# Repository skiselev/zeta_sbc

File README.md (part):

## Introduction

Zeta SBC V2 is a redesigned version of [Zeta SBC](http://www.malinov.com/Home/sergeys-projects/zeta-sbc). Compared to the first version this version features updated MMU with four banks, each one of those banks can be mapped to any 16 KiB page in 1 MiB on-board memory. It adds Z80 CTC which is used for generating periodic interrupts and as a vectored interrupt controller for UART and PPI. The FDC is replaced with 37C65. Compared to FDC9266 used in Zeta SBC it integrates input/output buffers and floppy disk control latch. Additionally 37C65 FDC is easier to obtain than FDC9266. And lastly it is made using CMOS technology and more power efficient than FDC9266

## Pictures

### Complete Board

### Zeta SBC with ParPortProp and a Floppy Drive

(FIXME: Picture shows Zeta SBC V1. Replace with Zeta SBC V2 when available.)

# Specifications

Zeta SBC V2 features following components:

* Z80 CPU
* 16550 UART - for connecting a console
* 8255 PPI - can be used for attaching a ParPortProp board, a hard drive using PPIDE or controlling some external devices
* Z80 CTC - can be used to generate periodic interrupts, and as an interrupt controller for UART and PPI
* Western Digital WD37C65, SMC FDC37C65, or GoldStar GM82C765B floppy disk controller.
* 512 KiB of battery backed SRAM
* 512 KiB of flash memory
* RTC

Zeta SBC V2 is compact and easy to build:

* Footprint of an 3.5" floppy drive (100 mm x 170.18 mm) and PCB can be mounted under a 3.5" drive.
* Uses only through hole components.
* Assumes using commonly available 3.5" floppy drives (not many people have 5.25" drives and even less 8" ones). Although it should work with 5.25" drives too.
* Only 2 configuration jumpers.
* Easy to use flash memory instead of UV EPROM.
* PCB mounted connectors, no need to build cables.
* Uses widely available components
* An easy way to get a "taste" of CP/M era computing.

# Hardware Documentation

File downloads are at the bottom of this page.

## KiCad Design Files

[Zeta SBC V2 - KiCad - 2.0.zip](files/Zeta%20SBC%20V2%20-%20KiCad%20-%202.0.zip)

## Schematic

[Zeta SBC V2 - Schematic - Color - 2.0.pdf](files/Zeta%20SBC%20V2%20-%20Schematic%20-%20Color%20-%202.0.pdf)

### PCB Version 2.0

[Zeta SBC V2 - Board - Color - 2.0.pdf](files/Zeta%20SBC%20V2%20-%20Board%20-%20Color%20-%202.0.pdf)

[Zeta SBC V2 - Gerber - 2.0.zip](files/Zeta%20SBC%20V2%20-%20Gerber%20-%202.0.zip)

## Input/Output Ports

* 20h - 23h (aliases 24h - 27h) - CTC Registers
  - 20h: Channel 0
  - 21h: Channel 1
  - 22h: Channel 2
  - 23h: Channel 3
  - See **Interrupts** section for Zeta SBC V2 specific CTC implementation and programming notes
* 28h (aliases 29h - 2Fh) - FDC CCR Register
  - Write only
  - FIXME: Add detailed description
* 30h (aliases 32h, 34h, 36h) - FDC Main Status Register
* 31h (aliases 33h, 35h, 37h) - FDC Data Register
* 38h (aliases 39h - 3Fh)
  - Write - FDC Diginal Output Register (DOR), also known as latch.
    + FIXME: Add detailed description
  - Read - Pulse FDC's /DACK and TC control lines
    + This port should be read following FDC data transfer command (read, write, format, etc.) to properly terminate data transfer.
* 60h-63h (alias 64h-67h) - PPI Registers
* 68h-6Fh - UART Registers
* 70h (aliases 71h-77h) - RTC Registers
  - Write:
    + Bits 0-3 - unused
    + Bit 4 - RTC Chip Enable
    + Bit 5 - RTC Write Enable
    + Bit 6 - RTC Clock
    + Bit 7 - RTC Input
  - Read:
    + Bit 0 - RTC Output
    + Bits 1-5 - unused
    + Bit 6 - Configuration Jumper (JP1)
    + Bit 7 - Disk Changed (DC) output from floppy drive. This can be used by the OS to detect floppy disk change. In such case CP/M should be warm rebooted.
* 78h-7Bh (alias 7Ch-7Fh) - Memory page select registers.
  - Write only
  - 78h - MPGSEL_0 - Page select register for bank #0 (0000h - 3FFFh)
  - 79h - MPGSEL_1 - Page select register for bank #1 (4000h - 7FFFh)
  - 7Ah - MPGSEL_2 - Page select register for bank #2 (8000h - 0BFFFh)
  - 7Bh - MPGSEL_3 - Page select register for bank #3 (0C000h - 0FFFFh)
  - Note: While these registers implemented as 8-bit registers, only 7 lower bits are decoded on board. 6 of these are actually used by on board memory, which contains of 64 pages, 16 KiB each.
* 7Ch (aliases 7Dh-7Fh) - MPGENA - Enable memory paging
  - Bits 0:
    + 0 = Disable memory paging (default after reset). When memory paging is disabled the memory page 0 (lower 16 KiB of the Flash ROM) is mapped to all banks.
    + 1 = Enable memory paging. Make sure that memory page select registers are configured properly before enabling paging.
  - Bits 1-7 - unused

## Memory

Zeta SBC V2 features a 512 KiB Flash ROM, and 512 KiB SRAM. The Flash ROM is used for the boot loader, monitor, OS (CP/M and ZSDOS at this point), and ROM disk. The SRAM is battery-backed, and is used for applications and for a RAM disk.

### Memory Banks and Paging

The 64 KiB Z80 memory address space is divided into four 16 KiB memory banks:

* Bank #0 (0000h - 3FFFh
* Bank #1 (4000h - 7FFFh)
* Bank #2 (8000h - 0BFFFh)
* Bank #3 (0C000h - 0FFFFh)

The physical memory (512 KiB Flash ROM and 512 KiB SRAM) is divided into 16 KiB pages:

* Pages 0 - 31 are mapped to the Flash ROM: page #0 starts at ROM address 00000h, and page #31 ends at ROM address 7FFFFh.
* Pages 32 - 63 are mapped to the SRAM: page #32 starts at RAM address 00000h, and page #63 ends at RAM address 7FFFFh.

Page select registers are used to map physical memory pages to the banks in Z80 address space:

* MPGSEL_0 (78h) - Page select register for bank #0
* M PGSEL_1 (79h) - Page select register for bank #1
* M PGSEL_2 (7Ah) - Page select register for bank #2
* M PGSEL_3 (7Bh) - Page select register for bank #3

Following a power on or a hard reset the memory paging mechanism is disabled, and memory address lines MA19 - MA14 are pulled down. So that page #0 (ROM addresses 00000h to 03FFF) is mapped to all four banks. That page should contain a boot loader that (among other things) configures and enables memory paging. Once page select registers are configured properly the memory paging can be enabled by setting bit 1 of MPGENA (7Ch) register.

### Programming Notes

1. The content of page select registers is unknown after a power on or a reboot. These registers need to be initialized before enabling memory paging. During the initialization the page select register for bank #0 needs to be set to page #0. So that CPU continues to execute instructions from that page.
2. The page select registers are implemented as 8-bit registers. Only 7 lower bits are decoded by Zeta SBC V2 memory chip select logic, and only 6 lower bits are actually used to address the memory. For future compatibility it is recommended that two higher bits of page select registers will be set to

## Interrupts

Zeta SBC V2 uses CTC as the source of vectored interrupts. For interrupts to function properly Z80 needs to be set to **interrupt mode 2**.

* Channels 0 and 1 are chained together. So that channel 1 can be used to generate low-frequency periodic interrupts:
  - Channel's 0 CLK/TG input is connected to UART_CLK/2 signal (921.6 kHz frequency)
  - Channel's 1 CLK/TG input in connected to c hannel's 0 ZC/TO output
* Channels 2 and 3 are connected to UART and FDC interrupt outputs. They can be used to generate vectored interrupts for these controllers:
  - Channel's 2 CLK/TG input is connected to UART interrupt output
  - Channel's 3 CLK/TG input is connected to 8255 PPI port PC3. This port is used as the interrupt output in PPI modes 1 and 2.

### Programming CTC to Generate Periodic Interrupts

CTC can generate periodic interrupts by dividing CTC clock (921.6 kHz) using channels 0 and 1 configured in counter mode. The CTC clock is connected to the trigger input of channel 0, and the ZC (zero count) output of channel 0 is connected the trigger input of channel 1. So that channel 0 will divide the clock, and the resulting signal will be divided further using channel 1.

In this example channel 0 is programmed with time constant of 256, so it will divide the input clock by 256, resulting in 3.6 kHz pulses. The channel 1 is programmed with down counter of 240, and will divide 3.6 kHz clock by 240, resulting in 15 Hz signal. That channel is also programmed to generate an interrupt every time counter reaches 0.

* Output `01000111 `to the channel 0. Configure the channel in the counter mode.
* Output `00000000&#xA0;`to the channel 0. Set the time constant to 256.
* Output `11000111 `to the channel 1. Configure the channel in the counter mode and enable interrupt when counter reaches 0.
* Output `11110000` to the channel 1. Set the time constant to 240, so that the interrupt will be generated every 1/15 of a second.
* Output `VVVVV000&#xA0;`to the channel 0. Set bits 7-3 of the interrupt vector. Bits 15-8 are set to the value of I register, bits 2 and 1 are set to the CTC channel number that caused the interrupt. Bit 0 is always 0. Note that each interrupt vector takes 2 bytes of memory and it should start on an even address.

### Programming CTC as an Interrupt Controller

CTC can be used as interrupt controller for UART and 8255 PPI using channels 2 and 3 respectively. In this case a CTC channel needs to be programmed for counter mode operation with time constant of 1. So that the first transition on CLK/TG input will result in counter going to 0 and CTC generating an interrupt.

* Output `110L0111` to the selected channel. This configures the channel in the counter mode with interrupts enabled. Bit 4 (L) sets the triggering edge: 0 - falling edge; 1 - rising edge.
* Output `00000001` to the selected channel. This loads value 1 to the time constant, so that an interrupt will be generated after detecting the first edge on the trigger input.
* Output `VVVVV000&#xA0;`to the channel 0. This sets bits 7-3 of the interrupt vector. Bits 15-8 are set to the I register, bits 2 and 1 are set to the CTC channel number that caused the interrupt. Bit 0 is always 0. Note that each interrupt vector takes 2 bytes of memory and it should start on an even address.

## Real Time Clock

Zeta SBC V2 includes a Maxim DS1302 RTC chip for timekeeping. It uses a CR2032 battery for power backup. The DS1302 has a 3-wire serial interface, and it is programmed through the RTC register (70h) using bit-banging. See Input/Output Ports section for the RTC register description. Please refer to [DS1302 datasheet](http://datasheets.maximintegrated.com/en/ds/DS1302.pdf) for programming information, and to the RomWBW (dsrtc.asm) for an RTC interface implementation.

## Jumpers and Connectors

### Jumper JP1 - CONFIG

JP1 is a software configuration jumper. It can be read by software using RTC port (70h) bit 6. This jumper is used by the RomWBW firmware with the ParPortProp support to configure the console device: it will use UART when this jumper is installed, and ParPortProp / VGA terminal when the jumper is not installed.

### Jumper JP2 - PIN25_GND/VCC

JP2 connects pin 25 of the parallel port P4 to either GND or Vcc (+5). Note that pin 1 is the pin that is closer to the parallel connector.

Warning: If JP2 is set incorrectly, it is possible to create a short circuit of the 5 Volt power supply.

| **Jumper Position** | **Description** |
| :------------------ | :-------------- |
| 1-2 | P4 pin 25 is connected to the ground |
| 2-3 | P4 pin 25 is connected to Vcc. Use this position with PPIDE, make sure to set jumper K1 on PPIDE to position 2-3. Please refer to [PPIDE documentation](https://sites.google.com/w/file/28373213/ppide-Install.txt) for more information. |
| **no jumper*** | P4 pin 25 is left open |

\* default

### Connector P1 - POWER

Connect regulated +5V power supply to this connector.

| Pin | Description |
| :-- | :---------- |
| tip (the inner contact) | Positive terminal - +5V |
| barrel / sleeve | Negative terminal - ground |

### Connector P2 - RESET

P2 is a connector for an external reset button.

### Connector P3 - SERIAL

P3 is the serial port connector. It is normally used for connecting a console or terminal. P3 uses pinout similar to that of IBM AT serial port (with some signals missing). Use a null modem cable to connect to a PC.

| **Pin Number** | **Signal Name** | **Description and Notes** |
| :------------- | :-------------- | :------------------------ |
| 1 | DCD | Carrier Detect; Not used - Not connected on the SBC |
| **2** | **RX** | **Receive Data; Input to SBC** |
| **3** | **TX** | **Transmit Data; Output from SBC** |
| 4 | DTR | Data Terminal Ready;Not used - Not connected on the SBC |
| **5** | **Signal Ground** | **Connected to the SBC GND signal** |
| 6 | DSR | Data Set Ready;Not used - Not connected on the SBC |
| **7** | **RTS** | **Request to Send; Output from SBC** |
| **8** | **CTS** | **Clear to Send; Input to SBC** |
| 9 | RI | Ring Indicator;Not used - Not connected on the SBC |
| **Shield** | **DE9 Shield** | **Connected to the SBC GND signal** |

### Connector P4 - PARALLEL

P4 is the parallel port connector. It is connected directly to the 8255 PPI and can be used for attaching, a ParPortProp board, an IDE hard disk using the PPIDE mini board, or for controlling external devices (e.g. printer, watering system), or for extending the SBC (e.g. connecting an LCD display and a keyboard). The pinout of P4 is the same as in other N8VEM boards (SBC V1, SBC V2, SBC-188).

| **Pin Number** | **Description** | **Pin Number** | **Description** | **Pin Number** | **Description** | **Pin Number** | **Description** |
| :------------- | :-------------- | :------------- | :-------------- | :------------- | :-------------- | :------------- | :-------------- |
| 1 | PC0 | 9 | PC4 | 17 | PB7 | 25 | GND or VCC (see JP2) |
| 2 | PA0 | 10 | PA4 | 18 | PB0 | 26 | GND |
| 3 | PC1 | 11 | PC5 | 19 | PB6 |  |  |
| 4 | PA1 | 12 | PA5 | 20 | PB1 |  |  |
| 5 | PC2 | 13 | PC6 | 21 | PB5 |  |  |
| 6 | PA2 | 14 | PA6 | 22 | PB2 |  |  |
| 7 | PC3 | 15 | PC7 | 23 | PB4 |  |  |
| 8 | PA3 | 16 | PA7 | 24 | PB3 |  |  |

### Connector P5 - FLOPPY

P5 is the floppy interface connector. It uses PC compatible pinout. When using a PC floppy cable with a twist, Drive A (ID 0) is the drive after the twist and Drive B (ID 1) is the drive before the twist. When using only one FDD, either a twisted cable can be used, or the BIOS can be patched to use Drive B.

| **Pin Number** | **Description** | **Direction (relative to the SBC)** | **Connected to** |
| :------------- | :-------------- | :---------------------------------- | :--------------- |
| 1-33 | Odd pins are GND |  | GND |
| 2 | High Density. This signal is ignored by most (all?) 3.5" drives. | Output | DOR (bit 6) |
| 4, 6 | Not used |  | No connection |
| 8 | Index Pulse | Input | Schmidt Trigger, FDC (IDX) |
| 10 | Motor On B | Output | DOR (bit 1), Buffer |
| 12 | Drive Select A | Output | FDC (US0, US1), Decoder |
| 14 | Drive Select B | Output | FDC (US0, US1), Decoder |
| 16 | Motor On A | Output | DOR (bit 1), Buffer |
| 18 | Direction | Output | FDC (LCT/DIR), Multiplexer |
| 20 | Step | Output | FDC (FR/STEP), Multiplexer |
| 22 | Write Data | Output | FDC (WDOUT), OC Buffer |
| 24 | Write Enable | Output | FDC (WE), OC Buffer |
| 26 | Track Zero | Input | Multiplexer, FDC (FLT/TR0) |
| 28 | Write Protect | Input | Multiplexer, FDC (WP/TS) |
| 30 | Read Data | Input | Schmidt Trigger, FDC (~DSKD) |
| 32 | Select Head | Output | FDC (HD), OC Buffer |
| 34 | Disk Changed | Input | DIR (bit 0) |

### Connector P6 - 5V

P6 is the 5V power output for the floppy drive. Alternatively it can be used instead of P1 for supplying power to the board. It is recommended to use a polarized header for P6 to avoid incorrect power polarity which probably will destroy FDD or components on the SBC board.

| **Pin Number** | **Description** |
| :------------- | :-------------- |
| 1 | 5V |
| 2 | GND |

**Warning P6 connector's key is reversed compared to Zeta SBC V 1.x. Please pay attention when upgrading from older boards. The polarity marking on the silkscreen is correct.**

## Bill of Materials (BOM)

### BOM Notes

Disclaimer: I did my best to make sure that components listed in this BOM will be compatible with Zeta SBC V2. Obviously I didn't order all of components listed here, and I was not able to actually verify that they will work. Please make sure to double check specifications on manufacturer's and seller's web site before ordering. Please let me know if you found any problems or incompatibilities.

Many components have multiple part numbers listed in BOM. There are some differences between various part numbers, such as:

* Different manufacturer. For example Texas Instruments vs. National Semiconductor for IC. Usually ICs built using the same technology will be 100% compatible. For some other components, for example connectors, sockets, or capacitors, it could be some difference in the quality. It is likely to get a better quality connector from TE (was AMP/Tyco) than from some obscure manufacturer (e.g. components sold under Jameco ValuePro brand).
* Specification differences
  - IC built using different different technologies (CMOS, TTL, NMOS) will have different specifications, and you might prefer to use certain IC family.
  - Difference in IC frequency or speed rating, especially for CPU, PPI, and memory.
  - Mechanical differences, especially for switches. Pick whatever suits best in your enclosure.
  - Some other minor differences. For example: RoHS or Pb-free vs. regular components; thickness of gold plating on connectors; frequency stability of oscillators and crystals.
* Price differences
  - For some reason some components are priced much higher than other otherwise similar parts.
  - One extreme example would be 512 KiB SRAM chips sold by Jameco (157358 and 242448) for almost $19 each, while AS6C4008-55PCN part sold by Mouser costs less than $5.
  - Some eBay sellers ask premium price for components because of their perceived uniqueness (keywords: vintage, rare, NOS, collectible), or special packaging (e.g. pink ceramic vs. plastic, gold plating).

If unsure what to order, read specifications on seller's and manufacturer's web sites. Also please read Replacement Notes below. Finally, consult people on [N8VEM news group](http://groups.google.com/group/n8vem).

## BOM

| **Component type** | **Reference** | **Description** | **Quantity** | **Possible sources and notes** |
| :----------------- | :------------ | :-------------- | :----------- | :----------------------------- |
| PCB |  | Zeta SBC V2 PCB Version 2.0 | 1 | Order from Sergey |
| Battery Holder | BT1 | CR2032 batter holder, 20 mm lead spacing | 1 | Mouser [122-2420-GR](http://www.mouser.com/ProductDetail/Eagle-Plastic-Devices/122-2420-GR/?qs=sGAEpiMZZMupuRtfu7GC%252beZOrkV%252bKN9%2FAB%252buxIS5wOM%3D "Click to view additional information on this product."),[122-2620-GR](http://www.mouser.com/ProductDetail/Eagle-Plastic-Devices/122-2620-GR/?qs=sGAEpiMZZMupuRtfu7GC%252bdT30ZRn29lxdufOO0Kb9bU%3D "Click to view additional information on this product.");Jameco [355434](http://www.jameco.com/webapp/wcs/stores/servlet/Product_10001_10001_355434_-1) |
| Capacitor | C1 - C24 | 0.1 uF ceramic, 5.08 mm lead spacing | 24 | Mouser [810-FK28X7R1H104K](http://www.mouser.com/search/refine.aspx?Keyword=810-FK28X7R1H104K),[80-C323C104K5R](http://www.mouser.com/ProductDetail/Kemet/C323C104K5R5TA/?qs=sGAEpiMZZMuAYrNc52CMZJc2YQhHPlYVWR1uyzMGvKQ%3D); Jameco [25523](http://www.jameco.com/webapp/wcs/stores/servlet/Product_10001_10001_25523_-1) |
| Capacitor | C25 | 47 uF, 6.3 V electrolytic | 1 | Mouser [667-ECA-1HHG470](http://www.mouser.com/ProductDetail/Panasonic-Electronic-Components/ECA-1HHG470/?qs=sGAEpiMZZMtZ1n0r9vR22be70OeCKE1EbiDEkso9tdM%3D "Click to view additional information on this product.");Jameco [31114](http://www.jameco.com/webapp/wcs/stores/servlet/Product_10001_10001_31114_-1) |
| Capacitor | C26 | 10 uF ceramic, 5.08 mm lead spacing | 1 | Mouser [810-FK24X5R1C106K](http://www.mouser.com/search/refine.aspx?Keyword=810-FK24X5R1C106K) Note: Can be replaced with tantalum or electrolytic capacitors |
| Diode | D1 | 1N4148 | 1 | Mouser [512-1N4148](http://www.mouser.com/ProductDetail/Fairchild-Semiconductor/1N4148/?qs=sGAEpiMZZMutXGli8Ay4kC4Bz7vbB60woGEFXf9TQ98%3D "Click to view additional information on this product."),[771-1N4148-T/R](http://www.mouser.com/ProductDetail/NXP-Semiconductors/1N4148113/?qs=sGAEpiMZZMutXGli8Ay4kE3wRMDwmh%2F%252bGmXBTkVQdt4%3D "Click to view additional information on this product.");Jameco [36038](http://www.jameco.com/webapp/wcs/stores/servlet/Product_10001_10001_36038_-1),[179215](http://www.jameco.com/webapp/wcs/stores/servlet/Product_10001_10001_179215_-1) |
| Diode | D2, D3 | Bi-level LED indicator | 1 | Mouser [696-SSF-LXH240GYD](http://www.mouser.com/ProductDetail/Lumex/SSF-LXH240GYD/?qs=sGAEpiMZZMurHQmwyojo5EtA%252bKO7aifq%2F8Iq2xqPbQI%3D "Click to view additional information on this product."); Jameco: Search for uni-color bi-level LED |
| Standoff | HOLE1, HOLE2, HOLE3, HOLE4 | Standoff, M3 male / female, 20 mm | 4 | Mouser [534-24317](http://www.mouser.com/ProductDetail/Keystone-Electronics/24317/?qs=sGAEpiMZZMs6x5FGDTpfsIdmmWiq5V9U4wJ1XZo48xk%3D "Click to view additional information on this product."),[534-25505](http://www.mouser.com/ProductDetail/Keystone-Electronics/25505/?qs=sGAEpiMZZMs6x5FGDTpfsIdmmWiq5V9Utxx9C%2Fw3Z7E%3D "Click to view additional information on this product."),[855-R30-3012002](http://www.mouser.com/ProductDetail/Harwin/R30-3012002/?qs=sGAEpiMZZMtzcnMBgC2bs6Id%2FK%2FNPiw4hN1Xmhg%2FQVw%3D "Click to view additional information on this product.") Note: The length of male end of these standoffs is 8 mm. It is too long for some floppy disk drives (you'll notice that standoff doesn't go completely inside the floppy drive mount hole). In this case cut a few millimeters using a file or a fine saw. |
| Screw | HOLE1, HOLE2, HOLE3, HOLE4 | Screw, M3, 6 mm | 4 | Use regular 3 mm floppy or CD-ROM drive mounting screws. Mouser [534-29311](http://www.mouser.com/ProductDetail/Keystone-Electronics/29311/?qs=sGAEpiMZZMs6x5FGDTpfsIdmmWiq5V9UXRwmMEDRMDY%3D) |
| Connector | JP1, P2 | 2x1 pin header | 2 | Mouser [649-78229-102HLF](http://www.mouser.com/ProductDetail/FCI/78229-102HLF/?qs=sGAEpiMZZMtsLRyDR9nM1%252b9K9ogxAkAjs2jx2M%252b94WE%3D "Click to view additional information on this product.");Jameco [108338](http://www.jameco.com/webapp/wcs/stores/servlet/Product_10001_10001_108338_-1) |
| Connector | JP2 | 3x1 pin header | 1 | Mouser [649-69190-103HLF](http://www.mouser.com/ProductDetail/FCI/69190-103HLF/?qs=sGAEpiMZZMvlX3nhDDO4AIYfP1TbgJhjYISz3bCP%2Fwo%3D "Click to view additional information on this product."),[649-78229-103HLF](http://www.mouser.com/ProductDetail/FCI/78229-103HLF/?qs=sGAEpiMZZMtsLRyDR9nM14Vjyw4ze%252bjtWzL%2FZN0BySE%3D "Click to view additional information on this product.");Jameco [109576](http://www.jameco.com/webapp/wcs/stores/servlet/Product_10001_10001_109576_-1) |
| Connector | P1 | DC jack | 1 | Mouser [806-KLDX-0202-A](http://www.mouser.com/ProductDetail/Kycon/KLDX-0202-A/?qs=sGAEpiMZZMu2f9RNbWupYrp4fVeNia8SgJaG%252bI5Hr1k%3D "Click to view additional information on this product.");Jameco [101178](http://www.jameco.com/webapp/wcs/stores/servlet/Product_10001_10001_101178_-1) |
| Connector | P3 | DE9M, right angle PCB mount | 1 | Mouser [806-K22X-E9P-N](http://www.mouser.com/ProductDetail/Kycon/K22X-E9P-N/?qs=sGAEpiMZZMu857ZbtCGHt0PbUrjjd%2FNBm0naypBlx9c%3D "Click to view additional information on this product."),[806-K22X-E9P-N-99](http://www.mouser.com/ProductDetail/Kycon/K22X-E9P-N-99/?qs=sGAEpiMZZMu857ZbtCGHt%2FwNqbkdXVI1Hsm1P%252bducYc%3D "Click to view additional information on this product.") (teal color),[571-7478404](http://www.mouser.com/ProductDetail/TE-Connectivity-AMP/747840-4/?qs=sGAEpiMZZMu857ZbtCGHtwpRvUYYjR%2Fb0tNi%2FPWGuJ4%3D "Click to view additional information on this product.");Jameco [104943](http://www.jameco.com/webapp/wcs/stores/servlet/Product_10001_10001_104943_-1),[614459](http://www.jameco.com/webapp/wcs/stores/servlet/Product_10001_10001_614459_-1),[614432](http://www.jameco.com/webapp/wcs/stores/servlet/Product_10001_10001_614432_-1); |
| Connector | P4 | 13x2 pin header | 1 | Mouser [649-68602-126HLF](http://www.mouser.com/ProductDetail/FCI/68602-126HLF/?qs=sGAEpiMZZMtsLRyDR9nM1%252bmbmmVUI0dAYWKlImNZbew%3D),[649-77313-824-26LF](http://www.mouser.com/ProductDetail/FCI/77313-824-26LF/?qs=sGAEpiMZZMtsLRyDR9nM14Vjyw4ze%252bjtilYVPfgiHws%3D);Jameco [53495](http://www.jameco.com/webapp/wcs/stores/servlet/Product_10001_10001_53495_-1) Note: don't use shrouded connector, as it will interfere with the standoff and other components. |
| Connector | P5 | 17x2 pin header shrouded | 1 | Mouser [517-30334-6002](http://www.mouser.com/ProductDetail/3M-Electronic-Solutions-Division/30334-6002HB/?qs=sGAEpiMZZMs%252bGHln7q6pmwu5ra4CY41if6I7inkHkkA%3d "Click to view additional information on this product."),[571-1033087](http://www.mouser.com/ProductDetail/TE-Connectivity/103308-7/?qs=sGAEpiMZZMs%252bGHln7q6pm48SVpWlpfsEybwRttC6%252baA%3d "Click to view additional information on this product."),[571-5103308-7](http://www.mouser.com/ProductDetail/TE-Connectivity/5103308-7/?qs=sGAEpiMZZMs%252bGHln7q6pm%252bE9wskmeR%2fSsajGI7pSzh4%3d "Click to view additional information on this product.");Jameco [68583](http://www.jameco.com/webapp/wcs/stores/servlet/Product_10001_10001_68583_-1),[753547](http://www.jameco.com/webapp/wcs/stores/servlet/Product_10001_10001_753547_-1) |
| Connector | P6 | 2 pin header with friction lock | 1 | Mouser [571-6404562](http://www.mouser.com/ProductDetail/TE-Connectivity-AMP/640456-2/?qs=sGAEpiMZZMtsLRyDR9nM16DGeeXFND9gHLFcjtDJkhM%3D),[571-3-641126-2](http://www.mouser.com/ProductDetail/TE-Connectivity-AMP/3-641126-2/?qs=sGAEpiMZZMtsLRyDR9nM18mJd%252baLxMG9uKUwnVJVJ8s%3D),[571-3-641215-2](http://www.mouser.com/ProductDetail/TE-Connectivity-AMP/3-641215-2/?qs=sGAEpiMZZMtsLRyDR9nM16DGeeXFND9gdDlMjBZrVXQ%3D);Jameco [232266](http://www.jameco.com/webapp/wcs/stores/servlet/Product_10001_10001_232266_-1),[613931](http://www.jameco.com/webapp/wcs/stores/servlet/Product_10001_10001_613931_-1); Corresponding female connector: Mouser [571-770602-2](http://www.mouser.com/ProductDetail/TE-Connectivity-AMP/770602-2/?qs=sGAEpiMZZMtsLRyDR9nM168vwp4yW2ZSGNK4xeaBpHA%3D);Jameco [234798](http://www.jameco.com/webapp/wcs/stores/servlet/Product_10001_10001_234798_-1)Contacts (2 contacts needed):Mouser [571-770666-1](http://www.mouser.com/ProductDetail/TE-Connectivity-AMP/770666-1/?qs=sGAEpiMZZMtsLRyDR9nM18mJd%252baLxMG9GrlfGo%252bW7aE%3D);Jameco [234923](http://www.jameco.com/webapp/wcs/stores/servlet/Product_10001_10001_234923_-1),[736501](http://www.jameco.com/webapp/wcs/stores/servlet/Product_10001_10001_736501_-1); It is recommended to use a polarized header to avoid incorrect power polarity. |
| Resistor | R1 | 10 Ohm, 1/4 W | 1 | Mouser [291-10-RC](http://www.mouser.com/ProductDetail/Xicon/291-10-RC/?qs=sGAEpiMZZMu61qfTUdNhG5WVxMYmJR0O1OUR1xbHmxs%3D);Jameco [690380](http://www.jameco.com/webapp/wcs/stores/servlet/Product_10001_10001_690380_-1) |
| Resistor | R2 | 10 kOhm, 1/4 W | 1 | Mouser [291-10K-RC](http://www.mouser.com/ProductDetail/Xicon/291-10K-RC/?qs=sGAEpiMZZMu61qfTUdNhG6xwTrVwTvbz8PPav3aExs8%3D); Jameco [691104](http://www.jameco.com/webapp/wcs/stores/servlet/Product_10001_10001_691104_-1) |
| Resistor | R3, R4 | 470 Ohm, 1/4 W | 2 | Mouser [291-470-RC](http://www.mouser.com/ProductDetail/Xicon/291-470-RC/?qs=sGAEpiMZZMu61qfTUdNhG1AdbDi3ermZfsjMZ8nKiDY%3D); Jameco [690785](http://www.jameco.com/webapp/wcs/stores/servlet/Product_10001_10001_690785_-1) |
| Resistor Array | RR1, RR2 | 1 kOhm, 6 pin, bussed resistor array | 2 | Mouser [264-1.0K-RC](http://www.mouser.com/ProductDetail/Xicon/264-10K-RC/?qs=sGAEpiMZZMvrmc6UYKmaNQbJ%252b29QTxaEngMB%2FdVaAdM%3D "Click to view additional information on this product."),[652-4306R-1LF-1K](http://www.mouser.com/ProductDetail/Bourns/4306R-101-102LF/?qs=sGAEpiMZZMvrmc6UYKmaNTNUNwWuH088chgRi4yNveI%3D "Click to view additional information on this product.") Note: When using CMOS U11, RR2 can have a higher value, for example 4.7k. This will reduce the power consumption. |
| Resistor Array | RR3, RR4 | 4.7 kOhm, 6 pin, bussed resistor array | 2 | Mouser [264-4.7K-RC](http://www.mouser.com/ProductDetail/Xicon/264-47K-RC/?qs=sGAEpiMZZMvrmc6UYKmaNVNDE5UWkgN%2FsgYW0PIGqes%3D "Click to view additional information on this product."),[652-4306R-1LF-4.7K](http://www.mouser.com/ProductDetail/Bourns/4306R-101-472LF/?qs=sGAEpiMZZMvrmc6UYKmaNWgIZ6biHU4EEgaZTof5r6w%3D "Click to view additional information on this product.") |
| Switch | SW1 | Tactile switch, right angle | 1 | Mouser [653-B3F-3100](http://www.mouser.com/ProductDetail/Omron-Electronics/B3F-3100/?qs=sGAEpiMZZMsgGjVA3toVBC93MDPUOLghd%252bGul%252bd9MzM%3d "Click to view additional information on this product."),[653-B3F-3152](http://www.mouser.com/ProductDetail/Omron-Electronics/B3F-3152/?qs=sGAEpiMZZMsgGjVA3toVBLOYoGzF1EI%252bcD5nMscmqSU%3d "Click to view additional information on this product."),[706-95C06A2RAT](http://www.mouser.com/ProductDetail/Grayhill/95C06A2RAT/?qs=sGAEpiMZZMsgGjVA3toVBGztKQtvElzogNtUxy25yuk%3d "Click to view additional information on this product."),[706-95C06C2RAT](http://www.mouser.com/ProductDetail/Grayhill/95C06C2RAT/?qs=sGAEpiMZZMsgGjVA3toVBGztKQtvElzoxqE4Q1H5TNc%3d "Click to view additional information on this product."),[706-95C06F2RAT](http://www.mouser.com/ProductDetail/Grayhill/95C06F2RAT/?qs=sGAEpiMZZMsgGjVA3toVBGztKQtvElzoEUXifV0kpgg%3d "Click to view additional information on this product.")Note: Switches can have different actuator length. You might want to select the switch according your own preferences, for example the enclosure type you want to use, and whatever you want the reset button to stick out of the enclosure or to stay hidden inside. Jameco [1953575](http://www.jameco.com/webapp/wcs/stores/servlet/Product_10001_10001_1953575_-1) |
| IC | U1 | Z80 CPU, CMOS, 40 pin DIP - Z84C00xxPEG | 1 | Mouser [692-Z84C0010PEG](http://www.mouser.com/ProductDetail/ZiLOG/Z84C0010PEG/?qs=sGAEpiMZZMvu0Nwh4cA1wSoSQ2enekUq2IMsKtAiEbo%3D),[692-Z84C0008PEG](http://www.mouser.com/ProductDetail/ZiLOG/Z84C0008PEG/?qs=sGAEpiMZZMvu0Nwh4cA1wWtRoPcQBaz3A%252bL%2FQ9ovAB8%3D); Jameco [35705](http://www.jameco.com/webapp/wcs/stores/servlet/Product_10001_10001_35705_-1),[35781](http://www.jameco.com/webapp/wcs/stores/servlet/Product_10001_10001_35781_-135781) Frequency of U17 (CPU clock) oscillator should be less or equal to CPU frequency. 8MHz CPU recommended for 1.44 MB floppy disks support. |
| IC | U2 | 512 KiB flash, 32 pin DIP - 39SF040,29F040, 29C040 | 1 | Mouser [804-39SF0407CPHE](http://www.mouser.com/ProductDetail/Microchip-Technology/SST39SF040-70-4C-PHE/?qs=sGAEpiMZZMtI%252bQ06EiAoGwr0W47sj3OOZ45%252baf2mLJ4%3D "Click to view additional information on this product."); Jameco [242667](http://www.jameco.com/webapp/wcs/stores/servlet/Product_10001_10001_242667_-1) |
| IC | U3 | 512 KiB SRAM, 32 pin DIP -AS6C4008-55PCN | 1 | Mouser [913-AS6C4008-55PCN](http://www.mouser.com/ProductDetail/Alliance-Memory/AS6C4008-55PCN/?qs=sGAEpiMZZMt9mBA6nIyysPeGHDtAZQ%252bHv1ODopTep98%3D) Note: Jameco 242448 and 157358 (BS62LV4006P) should work too, but they are way too expensive |
| IC | U4 | 16550 UART | 1 | Mouser [926-PC16550DN/NOPB](http://www.mouser.com/ProductDetail/Texas-Instruments/PC16550DN-NOPB/?qs=sGAEpiMZZMuyKkoWRCJ2WLeElKNr3DluUI5Xg6bwOh4%3d); Jameco [288809](http://www.jameco.com/webapp/wcs/stores/servlet/Product_10001_10001_288809_-1) |
| IC | U5 | 8255 PPI | 1 | Mouser [968-CP82C55AZ](http://www.mouser.com/ProductDetail/Intersil/CP82C55AZ/?qs=cbl4%252bYHJGOF3%2FjEgaAvGRe5K%2FILMXjQ3),[968-CP82C55A](http://www.mouser.com/ProductDetail/Intersil/CP82C55A/?qs=B4b5rvZIvWUoKcRPBZOAqTe8YvZ7Q5In); Jameco [52417](http://www.jameco.com/webapp/wcs/stores/servlet/Product_10001_10001_52417_-1) Unicorn Electronics (order 82C55) |
| IC | U6 | FDC, 40 pin DIP WD37C65, FDC37C65, GM82C765 | 1 | Buy from eBay |
| IC | U7 | Z80 CTC, CMOS, 28 pin DIP -Z84C30xxPEG | 1 | Mouser [692-Z84C3010PEG](http://www.mouser.com/ProductDetail/ZiLOG/Z84C3010PEG/?qs=sGAEpiMZZMtp5ziQ9mm%252bAlDnLybnUSNF),[692-Z84C3008PEG](http://www.mouser.com/ProductDetail/ZiLOG/Z84C3008PEG/?qs=sGAEpiMZZMsn4IaorHFpML59rb7vgZ39); Jameco [35609](http://www.jameco.com/webapp/wcs/stores/servlet/Product_10001_10001_35609_-1) |
| IC | U8, U9 | 74LS670 | 2 | Mouser [595-SN74LS670N](http://www.mouser.com/search/refine.aspx?Keyword=595-SN74LS670N),[771-HCT670N652](http://www.mouser.com/search/refine.aspx?Keyword=771-HCT670N652); Jameco [47976](http://www.jameco.com/webapp/wcs/stores/servlet/Product_10001_10001_47976_-1) Unicorn Electronics 74LS670 |
| IC | U10 | 74LS174 | 1 | Mouser [595-SN74ALS174N](http://www.mouser.com/ProductDetail/Texas-Instruments/SN74ALS174N/?qs=sGAEpiMZZMvxP%252bvr8KwMwH1qxRiYd9fqotp0hrbNkvI%3D),[595-SN74LS174N](http://www.mouser.com/ProductDetail/Texas-Instruments/SN74LS174N/?qs=sGAEpiMZZMvxP%252bvr8KwMwOIDaP0%252beD%2FyRsSdiADfoLM%3D),[595-SN74AHCT174N](http://www.mouser.com/ProductDetail/Texas-Instruments/SN74AHCT174N/?qs=sGAEpiMZZMvxP%252bvr8KwMwH1qxRiYd9fqkE7X46My71M%3D); Unicorn Electronics; Jameco [46931](http://www.jameco.com/webapp/wcs/stores/servlet/Product_10001_10001_46931_-1) |
| IC | U11 | 74ALS139 | 1 | Mouser [595-SN74ALS139N](http://www.mouser.com/ProductDetail/Texas-Instruments/SN74ALS139N/?qs=sGAEpiMZZMtxONTBFIcRfq4mebfZO%252bELhxGgXnQWC8c%3D),[595-SN74LS139AN](http://www.mouser.com/ProductDetail/Texas-Instruments/SN74LS139AN/?qs=sGAEpiMZZMtxONTBFIcRfpKvrGTByBdi%2FBZhV6RAyCA%3D),[595-CD74ACT139E](http://www.mouser.com/ProductDetail/Texas-Instruments/CD74ACT139E/?qs=sGAEpiMZZMtxONTBFIcRfsQCBiNmETR9yYy7yqk6Oio%3D),[595-SN74AHCT139N](http://www.mouser.com/ProductDetail/Texas-Instruments/SN74AHCT139N/?qs=sGAEpiMZZMtxONTBFIcRfsQCBiNmETR9s6YW4lCucrQ%3D); Unicorn Electronics; Jameco [46623](http://www.jameco.com/webapp/wcs/stores/servlet/Product_10001_10001_46623_-1),[301268](http://www.jameco.com/webapp/wcs/stores/servlet/Product_10001_10001_301268_-1) |
| IC | U12 | 74LS138 | 1 | Mouser [595-SN74ALS138AN](http://www.mouser.com/ProductDetail/Texas-Instruments/SN74ALS138AN/?qs=sGAEpiMZZMtxONTBFIcRfgMIbQHDmxevHm7M5LBU91I%3D),[595-SN74LS138N](http://www.mouser.com/ProductDetail/Texas-Instruments/SN74LS138N/?qs=sGAEpiMZZMtxONTBFIcRfpKvrGTByBdiQjlbb3Ynr4s%3D),[595-SN74AHCT138N](http://www.mouser.com/ProductDetail/Texas-Instruments/SN74AHCT138N/?qs=sGAEpiMZZMtxONTBFIcRfsQCBiNmETR9UG1XXuubiis%3D); Unicorn Electronics; Jameco [46607](http://www.jameco.com/webapp/wcs/stores/servlet/Product_10001_10001_46607_-1),[301233](http://www.jameco.com/webapp/wcs/stores/servlet/Product_10001_10001_301233_-1),[44927](http://www.jameco.com/webapp/wcs/stores/servlet/Product_10001_10001_44927_-1) |
| IC | U13 | 74LS125 | 1 | Mouser [595-SN74LS125AN](http://www.mouser.com/ProductDetail/Texas-Instruments/SN74LS125AN/?qs=sGAEpiMZZMuiiWkaIwCK2WAncryyStC7ZVuQLUtSxbI%3D),[595-SN74AHCT125N](http://www.mouser.com/ProductDetail/Texas-Instruments/SN74AHCT125N/?qs=sGAEpiMZZMuiiWkaIwCK2YBcf8bvyFlOxbSCg1DZEdI%3D); Unicorn Electronics; Jameco [46501](http://www.jameco.com/webapp/wcs/stores/servlet/Product_10001_10001_46501_-1) |
| IC | U14 | 74LS74 | 1 | Mouser [595-SN74ALS74AN](http://www.mouser.com/ProductDetail/Texas-Instruments/SN74ALS74AN/?qs=sGAEpiMZZMvxP%252bvr8KwMwD64K6n%252b0blWYVcQejy%2Fn2o%3D),[595-SN74AHCT74N](http://www.mouser.com/search/refine.aspx?Keyword=595-SN74AHCT74N); Jameco [48004](http://www.jameco.com/webapp/wcs/stores/servlet/Product_10001_10001_48004_-1),[295726](http://www.jameco.com/webapp/wcs/stores/servlet/Product_10001_10001_295726_-1),[45137](http://www.jameco.com/webapp/wcs/stores/servlet/Product_10001_10001_45137_-1) Unicorn Electronics 74ALS74, 74AHCT74 |
| IC | U15 | 74LS32 | 1 | Mouser [595-SN74ALS32N](http://www.mouser.com/ProductDetail/Texas-Instruments/SN74ALS32N/?qs=sGAEpiMZZMtMa9lbYwD6ZFfNaxHsgUwaIDUbKItpOSQ%3D),[595-SN74LS32N](http://www.mouser.com/ProductDetail/Texas-Instruments/SN74LS32N/?qs=sGAEpiMZZMtMa9lbYwD6ZOuZLcSXNpUacHuLMioAEnk%3D),[595-SN74ACT32N](http://www.mouser.com/ProductDetail/Texas-Instruments/SN74ACT32N/?qs=sGAEpiMZZMtMa9lbYwD6ZHl%252bb36l%252bC4R5ep%252b6HLRK5U%3d),[595-CD74ACT32E](http://www.mouser.com/ProductDetail/Texas-Instruments/CD74ACT32E/?qs=sGAEpiMZZMtMa9lbYwD6ZOqMILV%2fSzgW%252bsQ3Heghbw0%3d); Unicorn Electronics; Jameco [47466](http://www.jameco.com/webapp/wcs/stores/servlet/Product_10001_10001_47466_-1),[295515](http://www.jameco.com/webapp/wcs/stores/servlet/Product_10001_10001_295515_-1) |
| IC | U16 | 74LS14 | 1 | Mouser [595-SN74LS14N](http://www.mouser.com/ProductDetail/Texas-Instruments/SN74LS14N/?qs=sGAEpiMZZMuyBeSSR239Ias%252b1yN%2FIiBNAdJP0U6%2Fu9k%3D),[595-SN74AHCT14N](http://www.mouser.com/ProductDetail/Texas-Instruments/SN74AHCT14N/?qs=sGAEpiMZZMuyBeSSR239Ias%252b1yN%2FIiBNVP9ThiduLa4%3D); Unicorn Electronics; Jameco [46640](http://www.jameco.com/webapp/wcs/stores/servlet/Product_10001_10001_46640_-1),[295460](http://www.jameco.com/webapp/wcs/stores/servlet/Product_10001_10001_295460_-1),[44935](http://www.jameco.com/webapp/wcs/stores/servlet/Product_10001_10001_44935_-1) |
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
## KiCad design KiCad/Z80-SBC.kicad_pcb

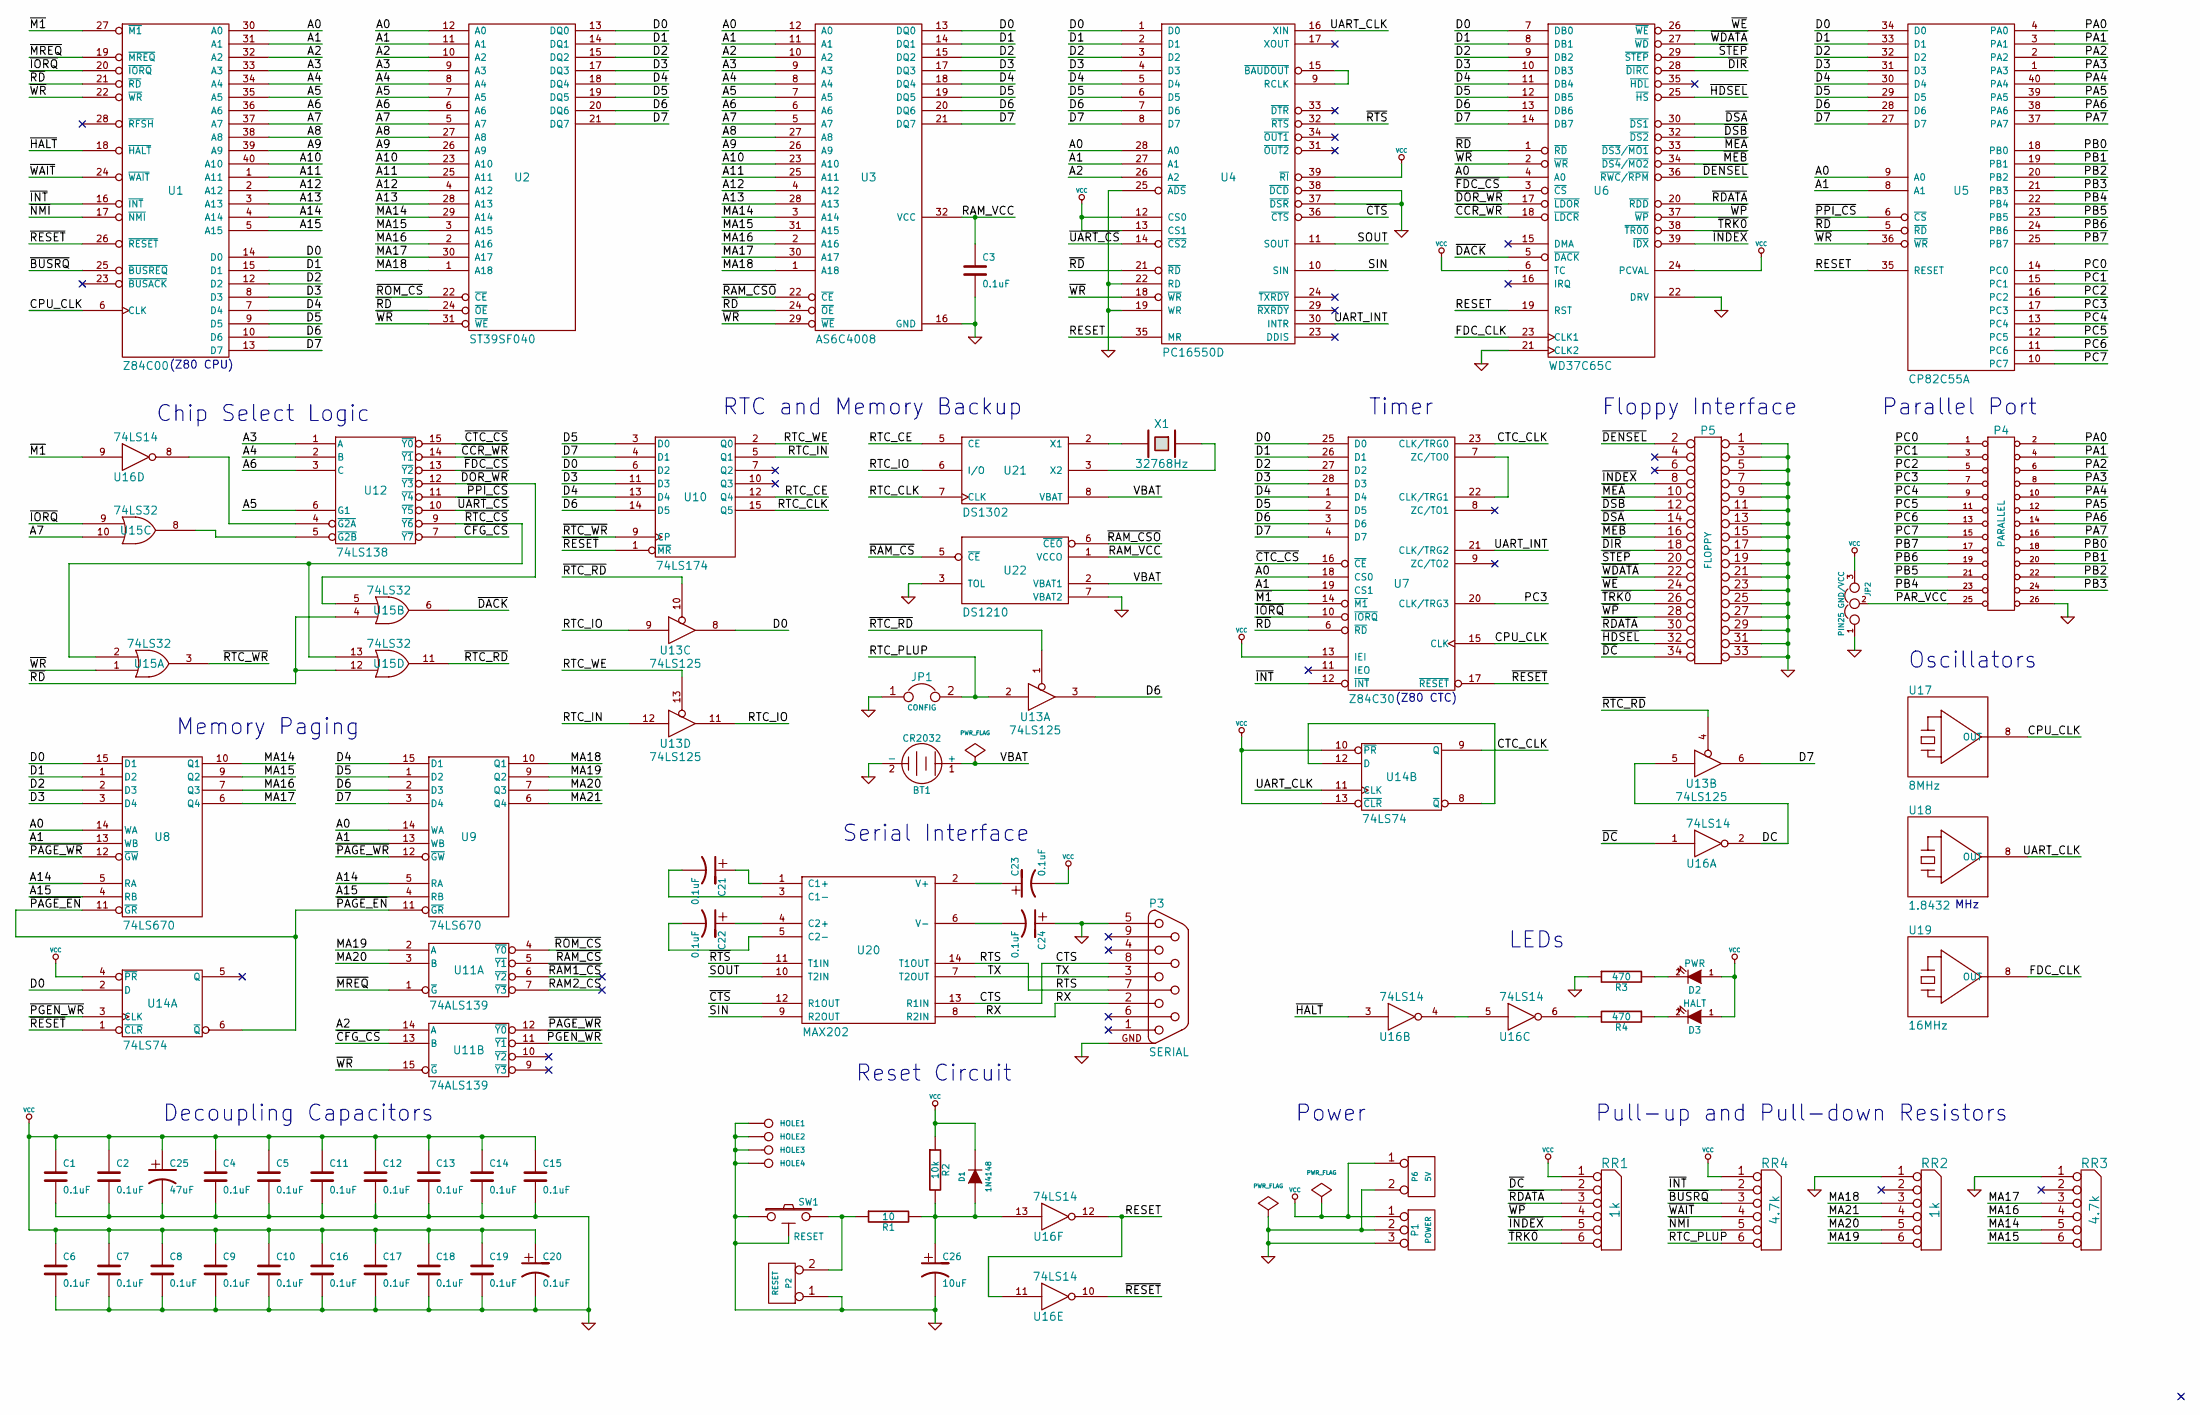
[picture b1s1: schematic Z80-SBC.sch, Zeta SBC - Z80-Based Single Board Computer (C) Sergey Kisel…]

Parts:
BT1: CR2032
C1, C2, C3, C4, C5, C6, C7, C8, C9, C10, C11, C12, C13, C14, C15, C16, C17, C18, C19, C20, C21, C22, C23, C24: 0.1uF
C25: 47uF
C26: 10uF
D1: 1N4148
D2: PWR
D3: HALT
HOLE1, HOLE2, HOLE3, HOLE4: CONN_1
JP1: CONFIG
JP2: PIN25 GND/VCC
P1: POWER
P2: RESET
P3: SERIAL
P4: PARALLEL
P5: FLOPPY
P6: 5V
R1: 10
R2: 10k
R3, R4: 470
RR1, RR2: 1k
RR3, RR4: 4.7k
SW1: RESET
U1: Z84C00
U2: ST39SF040
U3: AS6C4008
U4: PC16550D
U5: CP82C55A
U6: WD37C65C
U7: Z84C30
U8, U9: 74LS670
U10: 74LS174
U11: 74ALS139
U12: 74LS138
U13: 74LS125
U14: 74LS74
U15: 74LS32
U16: 74LS14
U17: 8MHz
U18: 1.8432
U19: 16MHz
U20: MAX202
U21: DS1302
U22: DS1210
X1: 32768Hz

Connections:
/A0: U1.30 (A0), U2.12 (A0), U3.12 (A0), U4.28 (A0), U5.9 (A0), U6.4 (A0), U7.18 (CS0), U8.14 (WA), U9.14 (WA)
/A1: U1.31 (A1), U2.11 (A1), U3.11 (A1), U4.27 (A1), U5.8 (A1), U7.19 (CS1), U8.13 (WB), U9.13 (WB)
/A2: U1.32 (A2), U2.10 (A2), U3.10 (A2), U4.26 (A2), U11.14 (A)
/A3: U1.33 (A3), U2.9 (A3), U3.9 (A3), U12.1 (A)
/A4: U1.34 (A4), U2.8 (A4), U3.8 (A4), U12.2 (B)
/A5: U1.35 (A5), U2.7 (A5), U3.7 (A5), U12.6 (G1)
/A6: U1.36 (A6), U2.6 (A6), U3.6 (A6), U12.3 (C)
/A7: U1.37 (A7), U2.5 (A7), U3.5 (A7), U15.10
/A8: U1.38 (A8), U2.27 (A8), U3.27 (A8)
/A9: U1.39 (A9), U2.26 (A9), U3.26 (A9)
/A10: U1.40 (A10), U2.23 (A10), U3.23 (A10)
/A11: U1.1 (A11), U2.25 (A11), U3.25 (A11)
/A12: U1.2 (A12), U2.4 (A12), U3.4 (A12)
/A13: U1.3 (A13), U2.28 (A13), U3.28 (A13)
/A14: U1.4 (A14), U8.5 (RA), U9.5 (RA)
/A15: U1.5 (A15), U8.4 (RB), U9.4 (RB)
/CPU_CLK: U1.6 (CLK), U7.15 (CLK), U17.8 (OUT)
/CTC_CLK: U7.23 (CLK/TRG0), U14.9 (Q)
/CTS: P3.8, U20.13 (R1IN)
/D0: U1.14 (D0), U2.13 (DQ0), U3.13 (DQ0), U4.1 (D0), U5.34 (D0), U6.7 (DB0), U7.25 (D0), U8.15 (D1), U10.6 (D2), U13.8, U14.2 (D)
/D1: U1.15 (D1), U2.14 (DQ1), U3.14 (DQ1), U4.2 (D1), U5.33 (D1), U6.8 (DB1), U7.26 (D1), U8.1 (D2)
/D2: U1.12 (D2), U2.15 (DQ2), U3.15 (DQ2), U4.3 (D2), U5.32 (D2), U6.9 (DB2), U7.27 (D2), U8.2 (D3)
/D3: U1.8 (D3), U2.17 (DQ3), U3.17 (DQ3), U4.4 (D3), U5.31 (D3), U6.10 (DB3), U7.28 (D3), U8.3 (D4), U10.11 (D3)
/D4: U1.7 (D4), U2.18 (DQ4), U3.18 (DQ4), U4.5 (D4), U5.30 (D4), U6.11 (DB4), U7.1 (D4), U9.15 (D1), U10.13 (D4)
/D5: U1.9 (D5), U2.19 (DQ5), U3.19 (DQ5), U4.6 (D5), U5.29 (D5), U6.12 (DB5), U7.2 (D5), U9.1 (D2), U10.3 (D0)
/D6: U1.10 (D6), U2.20 (DQ6), U3.20 (DQ6), U4.7 (D6), U5.28 (D6), U6.13 (DB6), U7.3 (D6), U9.2 (D3), U10.14 (D5), U13.3
/D7: U1.13 (D7), U2.21 (DQ7), U3.21 (DQ7), U4.8 (D7), U5.27 (D7), U6.14 (DB7), U7.4 (D7), U9.3 (D4), U10.4 (D1), U13.6
/DC: U13.5, U16.2
/FDC_CLK: U6.23 (CLK1), U19.8 (OUT)
/MA14: RR3.5, U2.29 (A14), U3.3 (A14), U8.10 (Q1)
/MA15: RR3.6, U2.3 (A15), U3.31 (A15), U8.9 (Q2)
/MA16: RR3.4, U2.2 (A16), U3.2 (A16), U8.7 (Q3)
/MA17: RR3.3, U2.30 (A17), U3.30 (A17), U8.6 (Q4)
/MA18: RR2.3, U2.1 (A18), U3.1 (A18), U9.10 (Q1)
/MA19: RR2.6, U9.9 (Q2), U11.2 (A)
/MA20: RR2.5, U9.7 (Q3), U11.3 (B)
/MA21: RR2.4, U9.6 (Q4)
/PA0: P4.2, U5.4 (PA0)
/PA1: P4.4, U5.3 (PA1)
/PA2: P4.6, U5.2 (PA2)
/PA3: P4.8, U5.1 (PA3)
/PA4: P4.10, U5.40 (PA4)
/PA5: P4.12, U5.39 (PA5)
/PA6: P4.14, U5.38 (PA6)
/PA7: P4.16, U5.37 (PA7)
/PAR_VCC: JP2.2, P4.25 (P24)
/PB0: P4.18, U5.18 (PB0)
/PB1: P4.20, U5.19 (PB1)
/PB2: P4.22, U5.20 (PB2)
/PB3: P4.24 (P20), U5.21 (PB3)
/PB4: P4.23, U5.22 (PB4)
/PB5: P4.21, U5.23 (PB5)
/PB6: P4.19, U5.24 (PB6)
/PB7: P4.17, U5.25 (PB7)
/PC0: P4.1, U5.14 (PC0)
/PC1: P4.3, U5.15 (PC1)
/PC2: P4.5, U5.16 (PC2)
/PC3: P4.7, U5.17 (PC3), U7.20 (CLK/TRG3)
/PC4: P4.9, U5.13 (PC4)
/PC5: P4.11, U5.12 (PC5)
/PC6: P4.13, U5.11 (PC6)
/PC7: P4.15, U5.10 (PC7)
/RAM_VCC: C3.1, U3.32 (VCC), U22.1 (VCCO)
/RESET: U4.35 (MR), U5.35 (RESET), U6.19 (RST), U16.11, U16.12
/RTC_CE: U10.12 (Q4), U21.5 (CE)
/RTC_CLK: U10.15 (Q5), U21.7 (CLK)
/RTC_IN: U10.5 (Q1), U13.12
/RTC_IO: U13.9, U13.11, U21.6 (I/O)
/RTC_PLUP: JP1.2, RR4.6, U13.2
/RTC_WE: U10.2 (Q0), U13.13
/RTS: P3.7, U20.14 (T1OUT)
/RX: P3.2, U20.8 (R2IN)
/SIN: U4.10 (SIN), U20.9 (R2OUT)
/SOUT: U4.11 (SOUT), U20.10 (T2IN)
/TX: P3.3, U20.7 (T2OUT)
/UART_CLK: U4.16 (XIN), U14.11 (CLK), U18.8 (OUT)
/UART_INT: U4.30 (INTR), U7.21 (CLK/TRG2)
/VBAT: BT1.1 (+), U21.8 (VBAT), U22.2 (VBAT1)
/~BUSRQ: RR4.3, U1.25 (~BUSREQ)
/~CCR_WR: U6.18 (~LDCR), U12.14 (~Y1)
/~CFG_CS: U11.13 (B), U12.7 (~Y7)
/~CTC_CS: U7.16 (~CE), U12.15 (~Y0)
/~CTS: U4.36 (~CTS), U20.12 (R1OUT)
/~DACK: U6.5 (~DACK), U15.6
/~DC: P5.34, RR1.2, U16.1
/~DENSEL: P5.2, U6.36 (~RWC~/~RPM~)
/~DIR: P5.18, U6.28 (~DIRC)
/~DOR_WR: U6.17 (~LDOR), U12.12 (~Y3), U15.5
/~DSA: P5.14, U6.30 (~DS1)
/~DSB: P5.12, U6.32 (~DS2)
/~FDC_CS: U6.3 (~CS), U12.13 (~Y2)
/~HALT: U1.18 (~HALT), U16.3
/~HDSEL: P5.32, U6.25 (~HS)
/~INDEX: P5.8, RR1.5, U6.39 (~IDX)
/~INT: RR4.2, U1.16 (~INT), U7.12 (~INT)
/~IORQ: U1.20 (~IORQ), U7.10 (~IORQ), U15.9
/~M1: U1.27 (~M1), U7.14 (~M1), U16.9
/~MEA: P5.10, U6.33 (~DS3~/~MO1~)
/~MEB: P5.16, U6.34 (~DS4~/~MO2~)
/~MREQ: U1.19 (~MREQ), U11.1 (~G)
/~NMI: RR4.5, U1.17 (~NMI)
/~PAGE_EN: U8.11 (~GR), U9.11 (~GR), U14.6 (~Q)
/~PAGE_WR: U8.12 (~GW), U9.12 (~GW), U11.12 (~Y0)
/~PGEN_WR: U11.11 (~Y1), U14.3 (CLK)
/~PPI_CS: U5.6 (~CS), U12.11 (~Y4)
/~RAM_CS: U11.5 (~Y1), U22.5 (~CE)
/~RAM_CSO: U3.22 (~CE), U22.6 (~CEO)
/~RD: U1.21 (~RD), U2.24 (~OE), U3.24 (~OE), U4.21 (~RD), U5.5 (~RD), U6.1 (~RD), U7.6 (~RD), U15.4, U15.12
/~RDATA: P5.30, RR1.3, U6.20 (~RDD)
/~RESET: U1.26 (~RESET), U7.17 (~RESET), U10.1 (~MR), U14.1 (~CLR), U16.10
/~ROM_CS: U2.22 (~CE), U11.4 (~Y0)
/~RTC_CS: U12.9 (~Y6), U15.2, U15.13
/~RTC_RD: U13.1, U13.4, U13.10, U15.11
/~RTC_WR: U10.9 (CP), U15.3
/~RTS: U4.32 (~RTS), U20.11 (T1IN)
/~STEP: P5.20, U6.29 (~STEP)
/~TRK0: P5.26, RR1.6, U6.38 (~TR00)
/~UART_CS: U4.14 (~CS2), U12.10 (~Y5)
/~WAIT: RR4.4, U1.24 (~WAIT)
/~WDATA: P5.22, U6.27 (~WD)
/~WE: P5.24, U6.26 (~WE)
/~WP: P5.28, RR1.4, U6.37 (~WP)
/~WR: U1.22 (~WR), U2.31 (~WE), U3.29 (~WE), U4.18 (~WR), U5.36 (~WR), U6.2 (~WR), U11.15 (~G), U15.1
GND: BT1.2 (-), C1.2, C2.2, C3.2, C4.2, C5.2, C6.2, C7.2, C8.2, C9.2, C10.2, C11.2, C12.2, C13.2, C14.2, C15.2, C16.2, C17.2, C18.2, C19.2, C20.2, C24.1, C25.2, C26.2, HOLE1.1, HOLE2.1, HOLE3.1, HOLE4.1, JP1.1, JP2.1, P1.2 (PM), P1.3, P2.1, P3.5, P3.GND, P4.26 (P22), P5.1, P5.3, P5.5, P5.7, P5.9, P5.11, P5.13, P5.15, P5.17, P5.19, P5.21, P5.23, P5.25, P5.27, P5.29, P5.31, P5.33, P6.2 (PM), R3.1, RR2.1 (COM), RR3.1 (COM), SW1.1, SW1.GND, U1.29 (GND), U2.16 (GND), U3.16 (GND), U4.19 (WR), U4.20 (GND), U4.22 (RD), U4.25 (~ADS), U4.37 (~DSR), U4.38 (~DCD), U5.7 (GND), U6.21 (CLK2), U6.22 (DRV), U6.31 (GND), U7.5 (GND), U8.8 (GND), U9.8 (GND), U10.8 (GND), U11.8 (GND), U12.8 (GND), U13.7 (GND), U14.7 (GND), U15.7 (GND), U16.7 (GND), U17.7 (GND), U18.7 (GND), U19.7 (GND), U20.15 (GND), U21.4 (GND), U22.3 (TOL), U22.4 (GND), U22.7 (VBAT2)
unnamed: C21.1, U20.1 (C1+)
unnamed: R4.2, U16.6
unnamed: C22.1, U20.4 (C2+)
unnamed: C23.1, U20.2 (V+)
unnamed: D3.2 (K), R4.1
unnamed: U12.4 (~G2A), U16.8
unnamed: U21.3 (X2), X1.1
unnamed: U4.9 (RCLK), U4.15 (~BAUDOUT)
unnamed: U21.2 (X1), X1.2
unnamed: P2.2 (PM), R1.1, SW1.2
unnamed: C26.1, D1.1 (A), R1.2, R2.2, U16.13
unnamed: U14.8 (~Q), U14.12 (D)
unnamed: D2.2 (K), R3.2
unnamed: U16.4, U16.5
unnamed: U7.7 (ZC/TO0), U7.22 (CLK/TRG1)
unnamed: C24.2, U20.6 (V-)
unnamed: C22.2, U20.5 (C2-)
unnamed: U12.5 (~G2B), U15.8
unnamed: C21.2, U20.3 (C1-)
VCC: C1.1, C2.1, C4.1, C5.1, C6.1, C7.1, C8.1, C9.1, C10.1, C11.1, C12.1, C13.1, C14.1, C15.1, C16.1, C17.1, C18.1, C19.1, C20.1, C23.2, C25.1, D1.2 (K), D2.1 (A), D3.1 (A), JP2.3, P1.1, P6.1, R2.1, RR1.1 (COM), RR4.1 (COM), U1.11 (VCC), U2.32 (VCC), U4.12 (CS0), U4.13 (CS1), U4.39 (~RI), U4.40 (VCC), U5.26 (VCC), U6.6 (TC), U6.24 (PCVAL), U6.40 (VCC), U7.13 (IEI), U7.24 (VCC), U8.16 (VCC), U9.16 (VCC), U10.16 (VCC), U11.16 (VCC), U12.16 (VCC), U13.14 (VCC), U14.4 (~PR), U14.10 (~PR), U14.13 (~CLR), U14.14 (VCC), U15.14 (VCC), U16.14 (VCC), U17.11 (VCC), U17.14 (VCC), U18.11 (VCC), U18.14 (VCC), U19.11 (VCC), U19.14 (VCC), U20.16 (VCC), U21.1 (VCC), U22.8 (VCC)

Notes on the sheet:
Pull-up and Pull-down Resistors
Power
Reset Circuit
LEDs
Parallel Port
Oscillators
Serial Interface
Floppy Interface
Decoupling Capacitors
RTC and Memory Backup
Chip Select Logic
Timer
Memory Paging
MHz
(Z80 CPU)
(Z80 CTC)

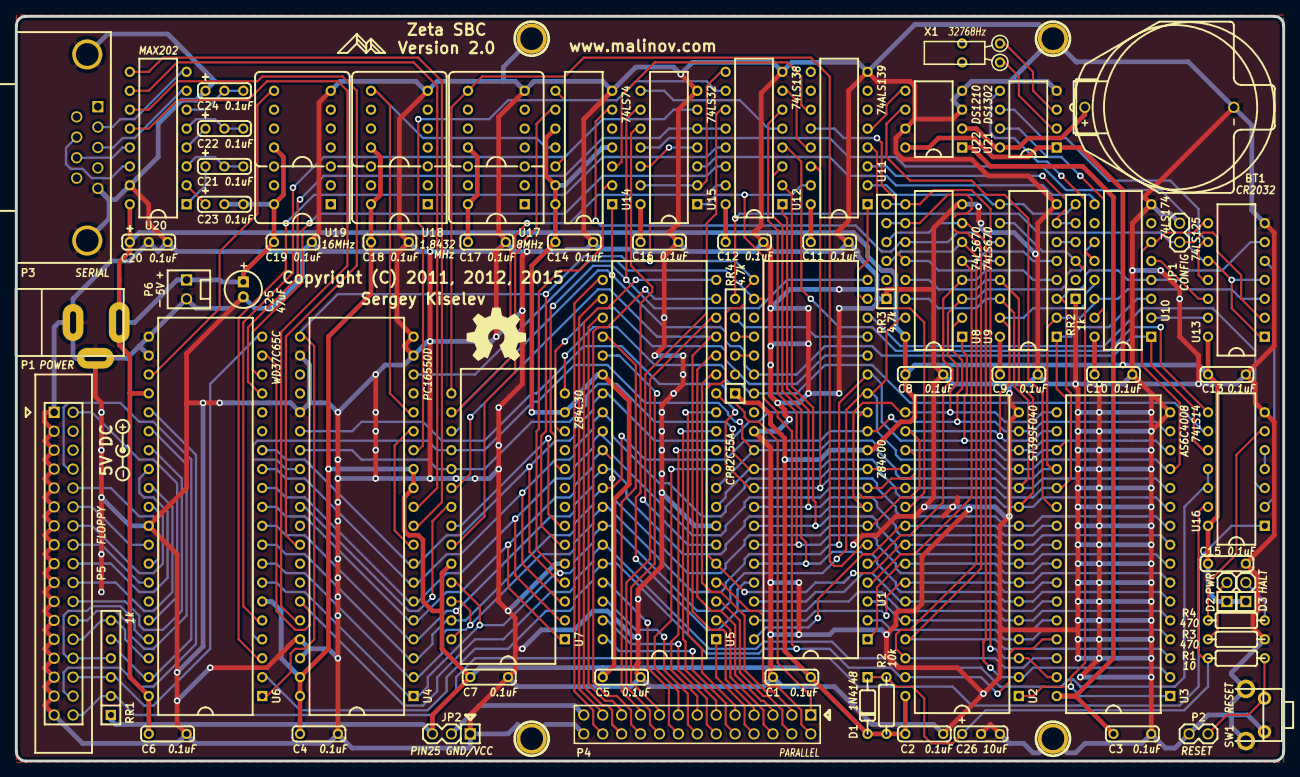
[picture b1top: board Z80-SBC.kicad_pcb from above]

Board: 2 copper layers, 170.2 x 100.0 mm, 74 parts (0 on the bottom side), 144 nets.

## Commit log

2020-02-10 printed_parts: Add OpenSCAD and STL files
2020-02-11 printed_parts: Add photos
2020-02-11 printed_parts: Create README
2022-03-01 Add website materials, unpack the 1.3 gerber and KiCad directories from zip
2022-03-01 Add V2 website materials, unpack the 2.0 gerber and KiCad directories from zip
2023-10-27 Add links to KiCad design, schematic, and PCB files

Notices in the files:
KiCad/Z80-SBC.kicad_pcb:
Copyright (C) 2011, 2012, 2015
